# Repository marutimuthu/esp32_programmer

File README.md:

<div align="center">
  
  <h2 align="center">ESP32 Programmer</h3>
  <p align="center">
    ⭐️ The Best ESP32 Serial Programmer ⭐️
    <br />
    
</div>

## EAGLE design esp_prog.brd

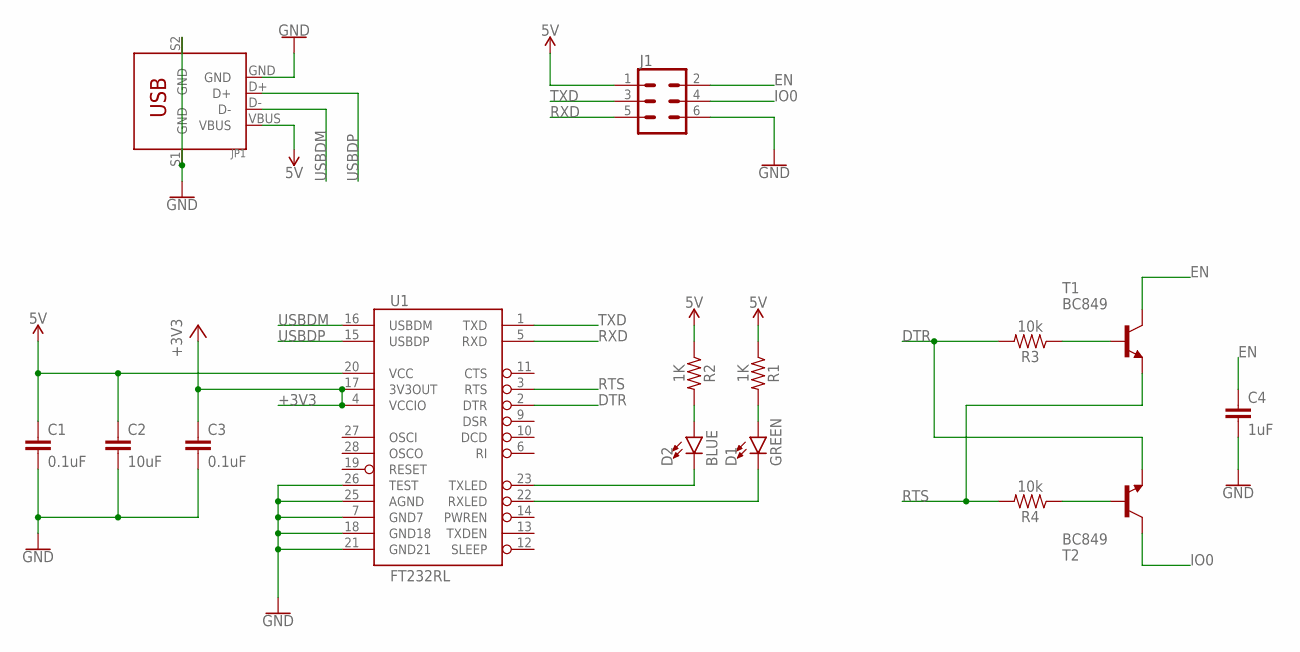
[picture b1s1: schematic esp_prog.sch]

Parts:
C1, C3: 0.1uF; 0603
C2: 10uF; 0603
C4: 1uF; 0603
D1: GREEN; LED-0603
D2: BLUE; LED-0603
J1: CONN_03X2SHROUD; 2X3-SHROUDED
JP1: DIP-USB-B-TYPE-FMAL(4+2P-2.0-90D); USB4+2-2.5-90D-15.8X12MM
R1, R2: 1K; 0603
R3, R4: 10k; 0603
T1, T2: BC849; SOT23
U1: FT232RL; SSOP28DB

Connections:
5V: C1.1, C2.1, J1.1, JP1.VBUS, R1.1, R2.1, U1.20 (VCC)
+3V3: C3.1, U1.4 (VCCIO), U1.17 (3V3OUT)
DTR: R3.2, T2.2 (E), U1.2 (DTR)
EN: C4.1, J1.2, T1.3 (C)
GND: C1.2, C2.2, C3.2, C4.2, J1.6, JP1.GND, JP1.S1 (GND), JP1.S2 (GND), U1.7 (GND7), U1.18 (GND18), U1.21 (GND21), U1.25 (AGND), U1.26 (TEST)
IO0: J1.4, T2.3 (C)
unnamed: D2.C, U1.23 (TXLED)
unnamed: D1.C, U1.22 (RXLED)
unnamed: D2.A, R2.2
unnamed: D1.A, R1.2
unnamed: R4.1, T2.1 (B)
unnamed: R3.1, T1.1 (B)
RTS: R4.2, T1.2 (E), U1.3 (RTS)
RXD: J1.5, U1.5 (RXD)
TXD: J1.3, U1.1 (TXD)
USBDM: JP1.D-, U1.16 (USBDM)
USBDP: JP1.D+, U1.15 (USBDP)

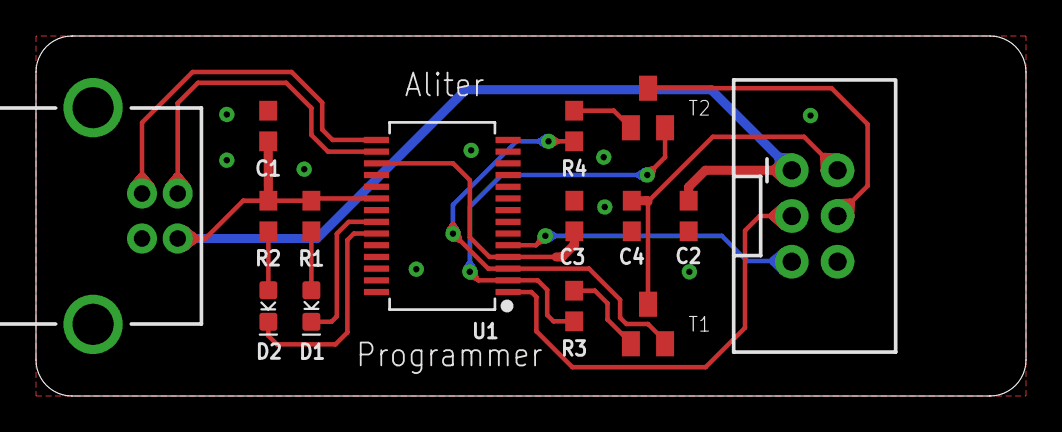
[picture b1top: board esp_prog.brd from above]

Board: 2 copper layers, 55.0 x 20.0 mm, 16 parts (1 on the bottom side), 17 nets.

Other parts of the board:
U$2: SFE_LUDUS-L

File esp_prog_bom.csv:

|----------------|-------------|---------|-------------|------|
| Device         |  Value      |  Legend |  Footprint  |  Qty |
|----------------|-------------|---------|-------------|------|
| Capacitor      |  0.1uF      | C1 C3   |  0603       |  2   |
|----------------|-------------|---------|-------------|------
| Capacitor      |  1uF        | C2 C4   |  0603       |  2   |
|----------------|-------------|---------|-------------|------
| Resistor       |  1K         | R1 R2   |  0603       |  1   |
|----------------|-------------|---------|-------------|------
| Resistor       |  10K        | R3 R4   |  0603       |  1   |
|----------------|-------------|---------|-------------|------
| LED            |  GREEN      |  D1     |  0603       |  1   |
|----------------|-------------|---------|-------------|------
| LED            |  BLUE       |  D2     |  0603       |  1   |
|----------------|-------------|---------|-------------|------
| Transistor NPN |  BC849      |  T1 T2  |  SOT23-3    |  2   |
|----------------|-------------|---------|-------------|------
| IC             |  FT232RL    |  U1     |  SSOP28     |  1   |
|----------------|-------------|---------|-------------|------
| CONNECTOR      |  2x3 Shroud |  J1     |  2X3 2.54mm |  1   |
|----------------|-------------|---------|-------------|------
| USB CONNECTOR  |  USB Type-B |  JP1    |  8x12mm     |  1   |
|----------------|-------------|---------|-------------|------

// F1 - Convert to table from CSV
Device, Value, Legend, Footprint, Qty
Capacitor, 0.1uF, "C1 C3", 0603, 2
Capacitor, 1uF, "C2 C4", 0603, 2
Resistor, 1K, "R1 R2", 0603, 1
Resistor, 10K, "R3 R4", 0603, 1
LED, GREEN, D1, 0603, 1
LED, BLUE, D2, 0603, 1
Transistor NPN, BC849, T1 T2, SOT23-3, 2
IC, FT232RL, U1, SSOP28, 1
CONNECTOR, 2x3 Shroud, J1, 2X3 2.54mm, 1
USB CONNECTOR, USB Type-B, JP1, 8x12mm, 1

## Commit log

2022-02-13 Updated Design, added gerber, schematic image, bom
2022-02-13 Changed 5V trace to 20 mil
2022-02-24 Changed 10uF in IO0 to 1uF in schematic, No change in Gerber
2022-02-24 Added LED indication silkscreen

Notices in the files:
parts and their libraries:
SparkFun-Capacitors: Licensing: Creative Commons ShareAlike 4.0 International - https://creativecommons.org/licenses/by-sa/4.0
